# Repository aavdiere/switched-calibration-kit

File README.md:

# Switched Calibration Kit (SCal)
DIY calibration module that automatically switches between calibration standards.
The idea is to use of the shelf RF switches with simple SMD resistors, which can be characterized using a reference measurement of a VNA and then used as a standard.

This is a data based approach is bound to imperfections. The other way would be to make a model of the calibration kit and reference that instead of a measurement.
As it is quite difficult to create a model for the switches without knowing the exact layout, the data approach was preferred.
The SCal is characterised and measured on the same day to avoid temperature fluctuations as they will impact the validity of the reference measurement, temperature control should be added on future revisions.

The boards were manufactured using Aisler's [four layer boards](https://community.aisler.net/t/4-layer-hd-pcb-stackup/86) using the Panasonic Prepreg 1080 Type R-1551(W).
The traces were designed to be 50Ω according to Aisler's recommendations.

## First version - Simple, cheap, proof of concept
Calibration kit using Infineon BGS12PN10/BGS14PN10.
- 2 ports
- 50 Ohm path
- Open path
- Short path
- Through path
- 3dB attenuation path

## Board

*Full populated board. High-end K (2.92mm) connectors were used but are definitely not required. Screw on connectors were used to reduce the solder variability during initial measurements.*

*Close-up picture of the switches and standards. The 50Ω terminations are made using two paralell 100Ω resistors on the bottom left and right. The 3dB attenuator path can be seen in the middle, formed as a Π-network.*

## Measurement method
- Perform ECal using the Keysight N4691D calibration kit and the PNA-X
- Measure all of the standards of the custom ECal and save data with calibration applied (reference) and not applied
- Measure the Rosenberger RPC 2.92mm and save data with calibration applied (reference) and not applied
- Attach additional cable to existing cables
- Measure all of the standards of the custom ECal and save raw data (no calibration, raw)
- Measure the Rosenberger RPC 2.92mm and save raw data (no calibration, raw)
- Using Python and scikit-rf package, create a TwelveTerm network calibration using the measured reference ECal standards as ideals and the measured raw ECal standards as measured
- Use this error network to calibrate out the raw measurements of the Rosenberger calibration kit and compare them with the reference measurements

An additional measurement would be a repeatability test:
- Repeatedly measure short/open/load/through standards, making sure you unscrew and screw a different standard in and out each time
- Create the error network using all possible combinations of these measurements
- Measure the variance in error network parameters
- Do the same with the ECal (screw/unscrew after each run), the variance in parameters should be lower considering you don't need to unscrew/screw after measuring each standard

## Results

*Raw measurements of each of the standards. From the open and the short the port offset is visible as is the frequency dependent loss. The through result shows the bandwidth associated with the switches as well as the traces.*

*Comparing the results from the SCal to the Keysight N4691D ECal, we can see comparible results, which look promising.*

*Differences in the measured load, somehow the SCal provides better results than the N4691D.*

*Here we can see the limitations of the measurements/switches. The measured through is nicely characterised up to around 3GHz, after which the SCal starts to deviate.*

## Remarks
The currently used silkscreen is confusing and prone to interconnection errors.
It might be a good idea to allow for rotational symmetry in the connector or to simply swap the legend around.

When looking at the load on the SCal, the S-parameters show that it starts of quite capacitive, which is odd.
This makes modelling it with typical methods difficult.
Maybe removing the whole top ground plane could fix that and only relying on microstrip lines.

The attenuator (not shown) doesn't have good performance, not even close.
Maybe using smaller resistors or a dedicated attenuator chip would be better.

The open and short standard should be located af far away from each other as possible as not to resonate.

The switches used have a minimum frequency in the datasheet.
This minimum frequency was ignored here and did not show up in the results.
However, if they are using PIN diodes to do the switching, the inductors used might not be good enough at lower frequencies, so watch out.

Overall the SCal has very nice results and could be usable for lower frequency measurements.

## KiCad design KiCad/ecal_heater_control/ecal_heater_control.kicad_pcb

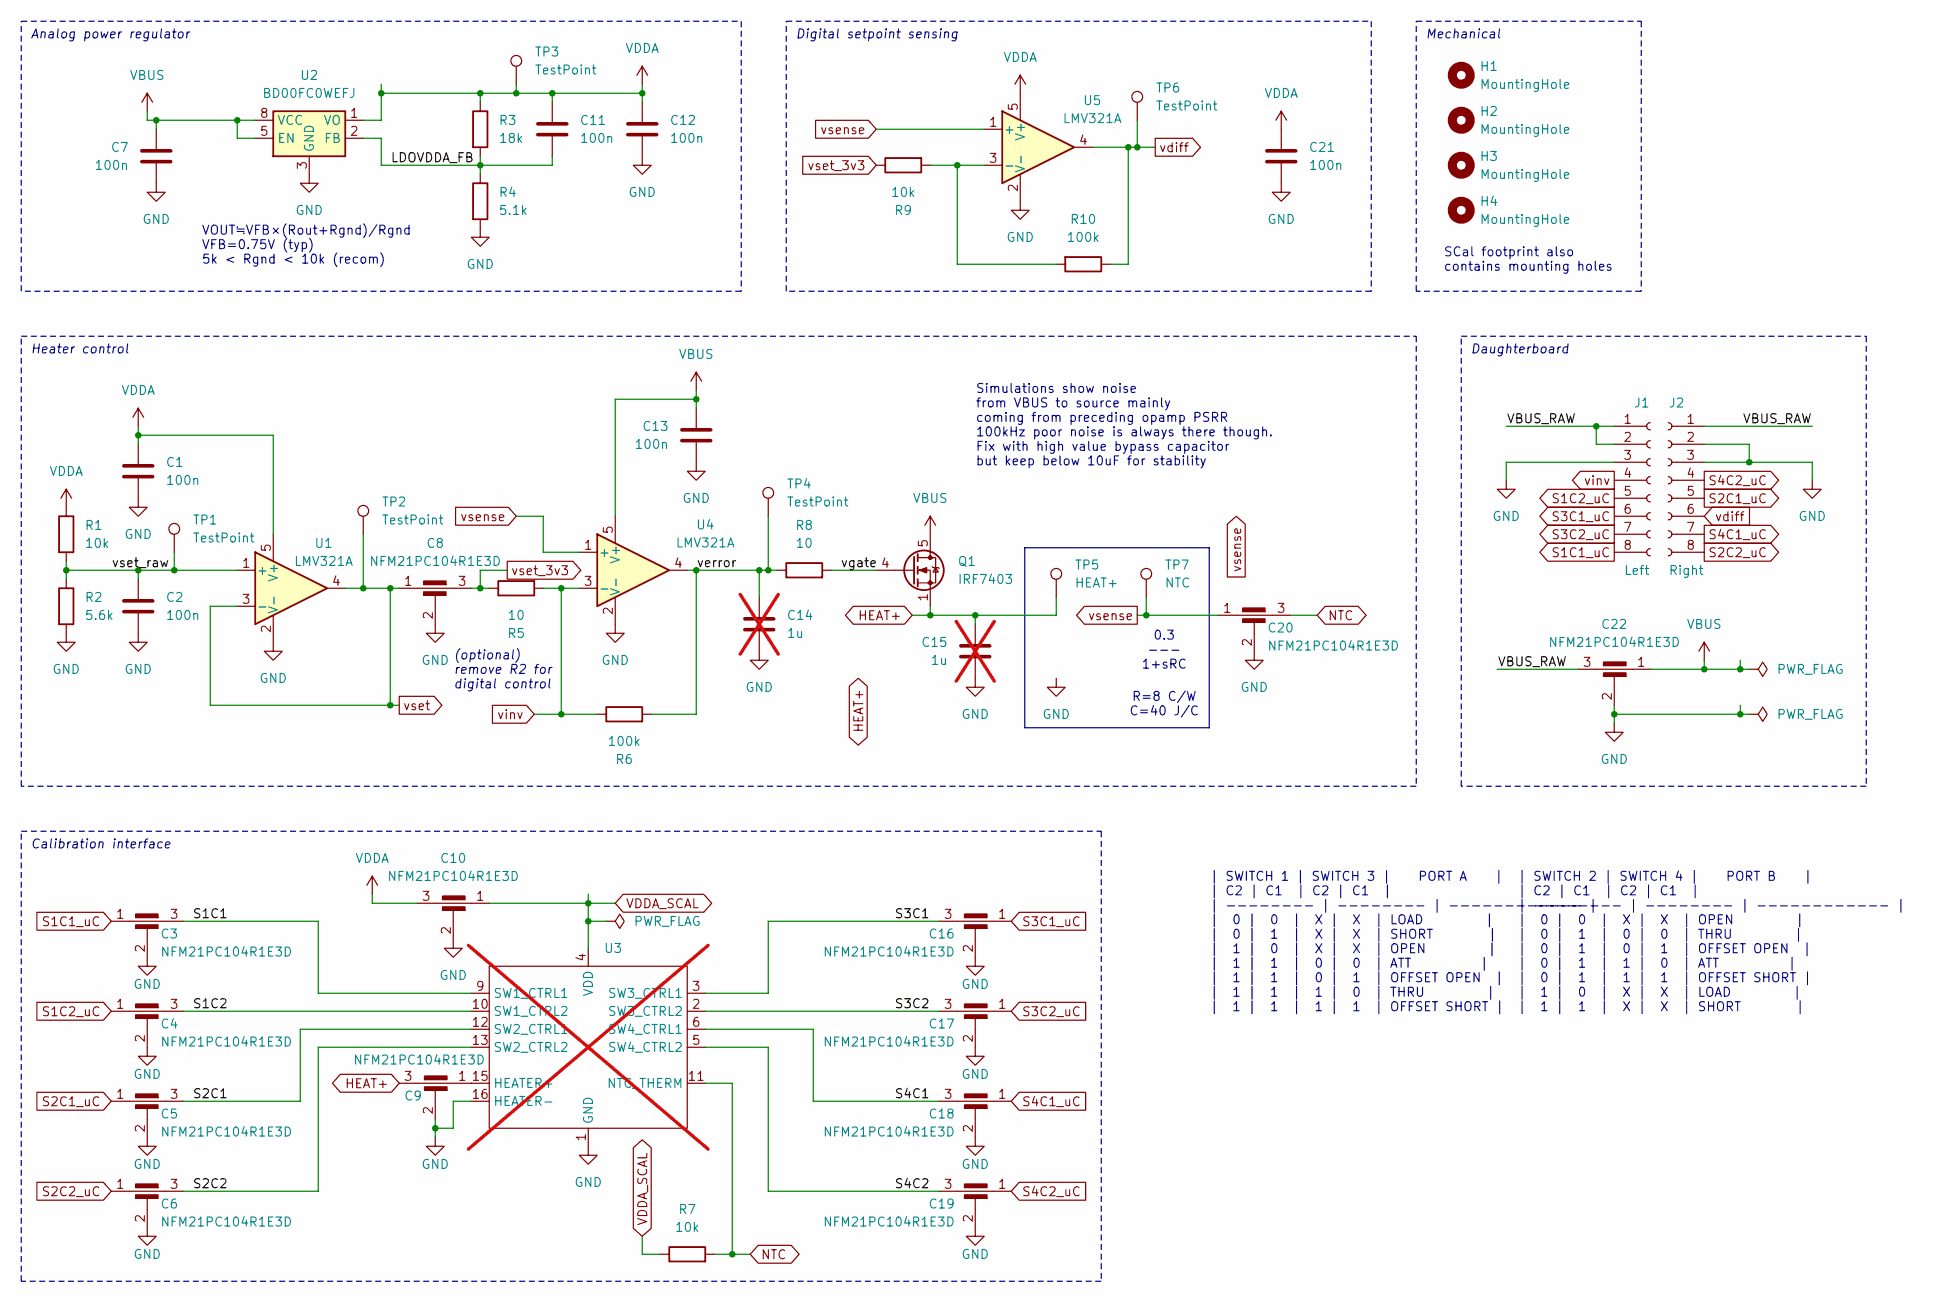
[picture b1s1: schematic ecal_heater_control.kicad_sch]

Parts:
C1, C2, C7, C11, C12, C13, C21: 100n; C_0402_1005Metric
C3, C4, C5, C6, C8, C9, C10, C16, C17, C18, C19, C20, C22: NFM21PC104R1E3D; NFM21PC
C14, C15: 1u; C_0603_1608Metric; not fitted
H1, H2, H3, H4: MountingHole; MountingHole_3.2mm_M3_DIN965
J1: Left; PinSocket_1x08_P2.54mm_Vertical
J2: Right; PinSocket_1x08_P2.54mm_Vertical
Q1: IRF7403; SOIC-8_3.9x4.9mm_P1.27mm
R1, R7, R9: 10k; R_0402_1005Metric
R2: 5.6k; R_0402_1005Metric
R3: 18k; R_0402_1005Metric
R4: 5.1k; R_0402_1005Metric
R5, R8: 10; R_0402_1005Metric
R6, R10: 100k; R_0402_1005Metric
TP1, TP2, TP3, TP4, TP6: TestPoint; TestPoint_Pad_D1.0mm
TP5: HEAT+; TestPoint_Pad_D1.0mm
TP7: NTC; TestPoint_Pad_D1.0mm
U1, U4, U5: LMV321A; SOT-23-5
U2: BD00FC0WEFJ; HTSOP-8-1EP_3.9x4.9mm_P1.27mm_EP2.4x3.2mm
U3: SCAL; not fitted

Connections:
/LDOVDDA_FB: C11.2, R3.2, R4.1, U2.2 (FB)
/S1C1: C3.3, U3.9 (SW1_CTRL1)
/S1C2: C4.3, U3.10 (SW1_CTRL2)
/S2C1: C5.3, U3.12 (SW2_CTRL1)
/S2C2: C6.3, U3.13 (SW2_CTRL2)
/S3C1: C16.3, U3.3 (SW3_CTRL1)
/S3C2: C17.3, U3.2 (SW3_CTRL2)
/S4C1: C18.3, U3.6 (SW4_CTRL1)
/S4C2: C19.3, U3.5 (SW4_CTRL2)
/VBUS_RAW: C22.3, J1.1, J1.2, J2.1
/verror: C14.1, R6.2, R8.1, TP4.1 (1_1), U4.4
/vgate: Q1.4 (G), R8.2
/vset_raw: C2.1, R1.2, R2.1, TP1.1 (1_1), U1.1 (+)
GND: C1.2, C2.2, C3.2, C4.2, C5.2, C6.2, C7.2, C8.2, C9.2, C10.2, C12.2, C13.2, C14.2, C15.2, C16.2, C17.2, C18.2, C19.2, C20.2, C21.2, C22.2, J1.3, J2.2, J2.3, R2.2, R4.2, U1.2 (V-), U2.3 (GND), U2.9 (GND), U3.1 (GND), U3.7 (GND), U3.8 (GND), U3.14 (GND), U3.16 (HEATER-), U4.2 (V-), U5.2 (V-)
HEAT+: C9.3, C15.1, Q1.1 (S), Q1.2 (S), Q1.3 (S), TP5.1 (1_1)
NTC: C20.3, R7.2, U3.11 (NTC_THERM)
unnamed: C9.1, U3.15 (HEATER+)
unnamed: R9.2, R10.2, U5.3 (-)
S1C1_uC: C3.1, J1.8
S1C2_uC: C4.1, J1.5
S2C1_uC: C5.1, J2.5
S2C2_uC: C6.1, J2.8
S3C1_uC: C16.1, J1.6
S3C2_uC: C17.1, J1.7
S4C1_uC: C18.1, J2.7
S4C2_uC: C19.1, J2.4
VBUS: C7.1, C13.1, C22.1, Q1.5 (D), Q1.6 (D), Q1.7 (D), Q1.8 (D), U2.5 (EN), U2.8 (VCC), U4.5 (V+)
VDDA: C1.1, C10.3, C11.1, C12.1, C21.1, R1.1, R3.1, TP3.1 (1_1), U1.5 (V+), U2.1 (VO), U5.5 (V+)
VDDA_SCAL: C10.1, R7.1, U3.4 (VDD)
vdiff: J2.6, R10.1, TP6.1 (1_1), U5.4
vinv: J1.4, R5.2, R6.1, U4.3 (-)
vsense: C20.1, TP7.1 (1_1), U4.1 (+), U5.1 (+)
vset: C8.1, TP2.1 (1_1), U1.3 (-), U1.4
vset_3v3: C8.3, R5.1, R9.1

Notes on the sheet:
Daughterboard
Digital setpoint sensing
VOUT≒VFB×(Rout+Rgnd)/Rgnd VFB=0.75V (typ) 5k < Rgnd < 10k (recom)
Heater control
0.3 --- 1+sRC
Analog power regulator
SCal footprint also contains mounting holes
Calibration interface
Simulations show noise from VBUS to source mainly coming from preceding opamp PSRR 100kHz poor noise is always there though. Fix with high value bypass capacitor but keep below 10uF for stability
(optional) remove R2 for digital control
R=8 C/W C=40 J/C
Mechanical
| SWITCH 1 | SWITCH 3 | PORT A | | C2 | C1 | C2 | C1 | | -------- | -------- | ------------ | | 0 | 0 | X | X | LOAD | | 0 | 1 | X | X | SHORT | | 1 | 0 | X | X | OPEN | | 1 | 1 | 0 | 0 | ATT | | 1 | 1 | 0 | 1 | OFFSET OPEN | | 1 | 1 | 1 | 0 | THRU | | 1 | 1 | 1 | 1 | OFFSET SHORT |
| SWITCH 2 | SWITCH 4 | PORT B | | C2 | C1 | C2 | C1 | | -------- | -------- | ------------ | | 0 | 0 | X | X | OPEN | | 0 | 1 | 0 | 0 | THRU | | 0 | 1 | 0 | 1 | OFFSET OPEN | | 0 | 1 | 1 | 0 | ATT | | 0 | 1 | 1 | 1 | OFFSET SHORT | | 1 | 0 | X | X | LOAD | | 1 | 1 | X | X | SHORT |

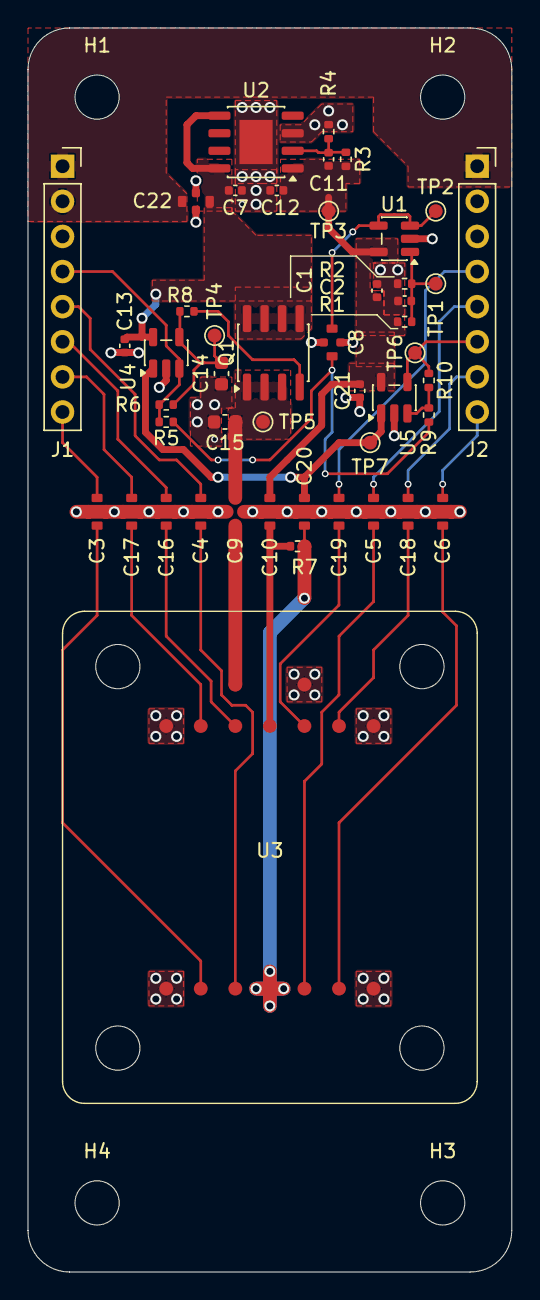
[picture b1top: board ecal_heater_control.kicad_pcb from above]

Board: 2 copper layers, 35.0 x 90.0 mm, 51 parts (0 on the bottom side), 34 nets.

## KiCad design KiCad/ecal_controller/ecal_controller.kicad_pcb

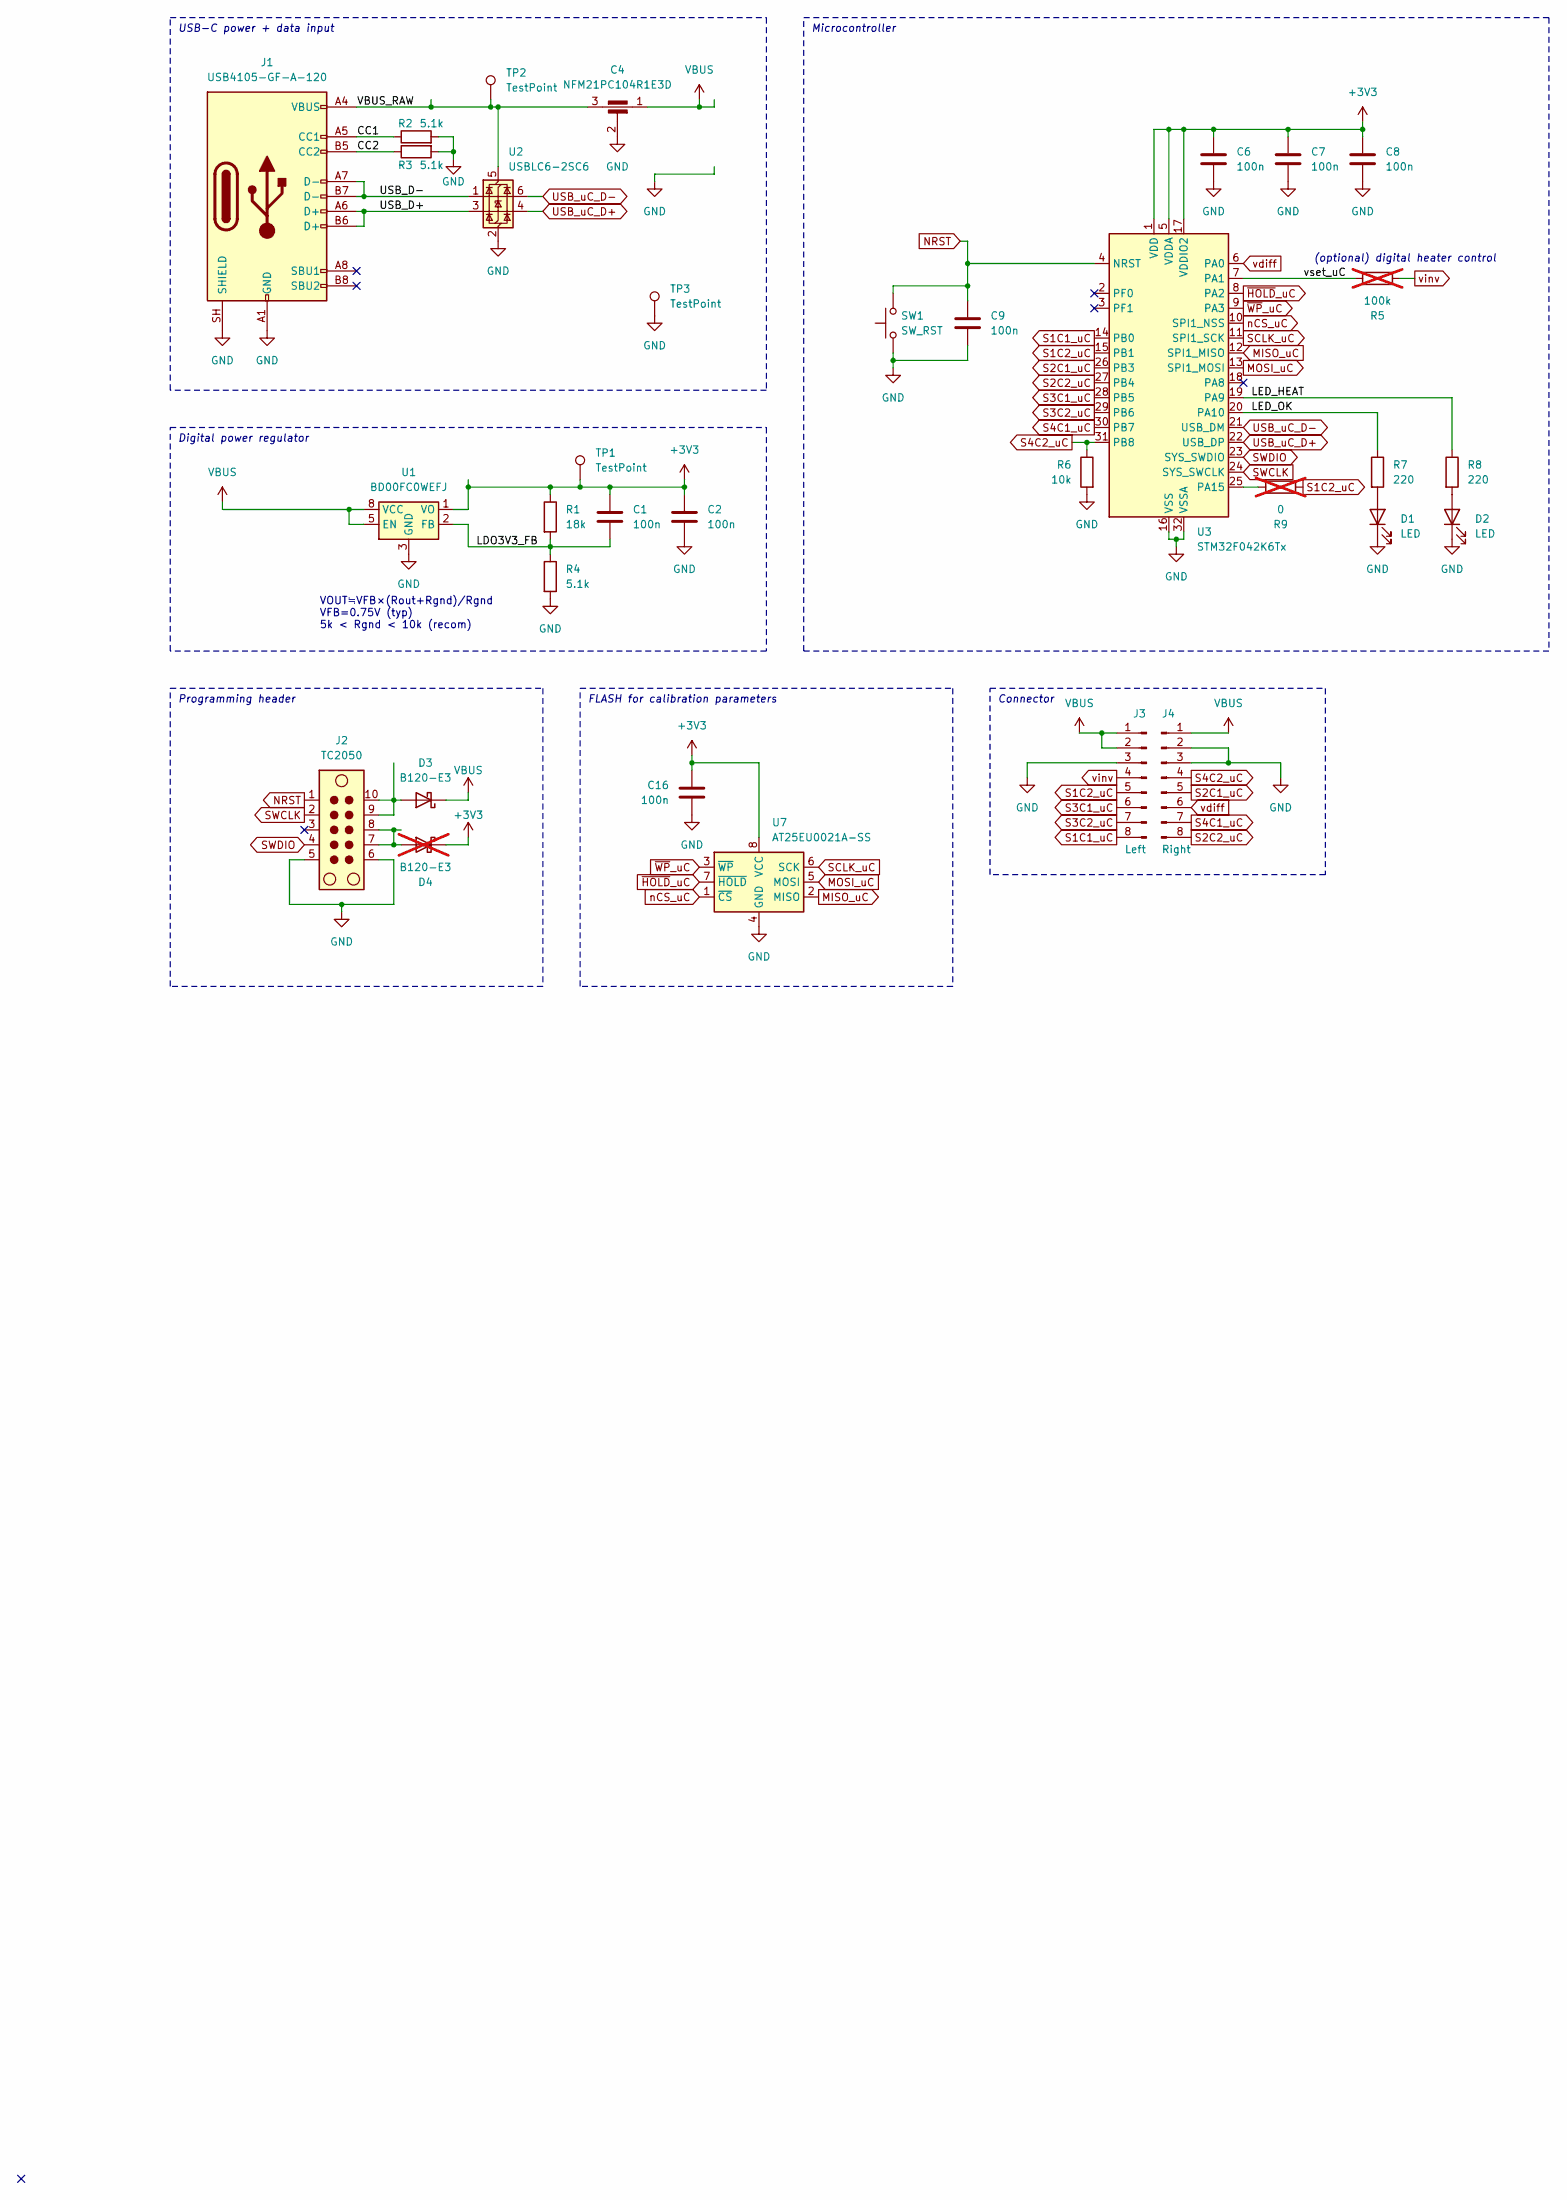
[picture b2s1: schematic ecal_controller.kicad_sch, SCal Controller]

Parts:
C1, C2, C6, C7, C8, C9, C16: 100n; C_0402_1005Metric
C4: NFM21PC104R1E3D; NFM21PC
D1, D2: LED; LED_0603_1608Metric
D3: B120-E3; D_SMA
D4: B120-E3; D_SMA; not fitted
J1: USB4105-GF-A-120; USB_C_Receptacle_GCT_USB4110
J2: TC2050; Tag-Connect_TC2050-IDC-FP_2x05_P1.27mm_Vertical
J3: Left; PinHeader_1x08_P2.54mm_Vertical
J4: Right; PinHeader_1x08_P2.54mm_Vertical
R1: 18k; R_0402_1005Metric
R2, R3, R4: 5.1k; R_0402_1005Metric
R5: 100k; R_0402_1005Metric; not fitted
R6: 10k; R_0402_1005Metric
R7, R8: 220; R_0402_1005Metric
R9: 0; R_0402_1005Metric; not fitted
SW1: SW_RST; SW_Push_1P1T_NO_E-Switch_TL3301NxxxxxG
TP1, TP2, TP3: TestPoint; TestPoint_Pad_D1.0mm
U1: BD00FC0WEFJ; HTSOP-8-1EP_3.9x4.9mm_P1.27mm_EP2.4x3.2mm
U2: USBLC6-2SC6; SOT-23-6
U3: STM32F042K6Tx; LQFP-32_7x7mm_P0.8mm
U7: AT25EU0021A-SS; SOIC-8_3.9x4.9mm_P1.27mm

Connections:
+3V3: C1.1, C2.1, C6.1, C7.1, C8.1, C16.1, D4.1 (K), R1.1, TP1.1 (1_1), U1.1 (VO), U3.1 (VDD), U3.5 (VDDA), U3.17 (VDDIO2), U7.8 (VCC)
/CC1: J1.A5 (CC1), R2.1
/CC2: J1.B5 (CC2), R3.1
/LDO3V3_FB: C1.2, R1.2, R4.1, U1.2 (FB)
/LED_HEAT: R8.1, U3.19 (PA9)
/LED_OK: R7.1, U3.20 (PA10)
/USB_D+: J1.A6 (D+), J1.B6 (D+), U2.3 (I/O2)
/USB_D-: J1.A7 (D-), J1.B7 (D-), U2.1 (I/O1)
/VBUS_RAW: C4.3, J1.A4 (VBUS), J1.A9 (VBUS), J1.B4 (VBUS), J1.B9 (VBUS), TP2.1 (1_1), U2.5 (VBUS)
/vset_uC: R5.1, U3.7 (PA1)
GND: C2.2, C4.2, C6.2, C7.2, C8.2, C9.2, C16.2, D1.1 (K), D2.1 (K), J1.A1 (GND), J1.A12 (GND), J1.B1 (GND), J1.B12 (GND), J1.SH (SHIELD), J2.5, J2.6, J3.3, J4.2, J4.3, R2.2, R3.2, R4.2, R6.2, SW1.1, TP3.1 (1_1), U1.3 (GND), U1.9 (GND), U2.2 (GND), U3.16 (VSS), U3.32 (VSSA), U7.4 (GND)
MISO_uC: U3.12 (SPI1_MISO), U7.2 (MISO)
MOSI_uC: U3.13 (SPI1_MOSI), U7.5 (MOSI)
NRST: C9.1, J2.1, SW1.2, U3.4 (NRST)
unnamed: D1.2 (A), R7.2
unnamed: D2.2 (A), R8.2
unnamed: D3.2 (A), J2.9, J2.10
unnamed: D4.2 (A), J2.7, J2.8
unnamed: R9.1, U3.25 (PA15)
S1C1_uC: J3.8, U3.14 (PB0)
S1C2_uC: J3.5, R9.2, U3.15 (PB1)
S2C1_uC: J4.5, U3.26 (PB3)
S2C2_uC: J4.8, U3.27 (PB4)
S3C1_uC: J3.6, U3.28 (PB5)
S3C2_uC: J3.7, U3.29 (PB6)
S4C1_uC: J4.7, U3.30 (PB7)
S4C2_uC: J4.4, R6.1, U3.31 (PB8)
SCLK_uC: U3.11 (SPI1_SCK), U7.6 (SCK)
SWCLK: J2.2, U3.24 (SYS_SWCLK)
SWDIO: J2.4, U3.23 (SYS_SWDIO)
USB_uC_D+: U2.4 (I/O2), U3.22 (USB_DP)
USB_uC_D-: U2.6 (I/O1), U3.21 (USB_DM)
VBUS: C4.1, D3.1 (K), J3.1, J3.2, J4.1, U1.5 (EN), U1.8 (VCC)
nCS_uC: U3.10 (SPI1_NSS), U7.1 (~CS)
vdiff: J4.6, U3.6 (PA0)
vinv: J3.4, R5.2
~HOLD_uC: U3.8 (PA2), U7.7 (~HOLD)
~WP_uC: U3.9 (PA3), U7.3 (~WP)

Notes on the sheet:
Digital power regulator
VOUT≒VFB×(Rout+Rgnd)/Rgnd VFB=0.75V (typ) 5k < Rgnd < 10k (recom)
USB-C power + data input
Programming header
FLASH for calibration parameters
Connector
(optional) digital heater control
Microcontroller

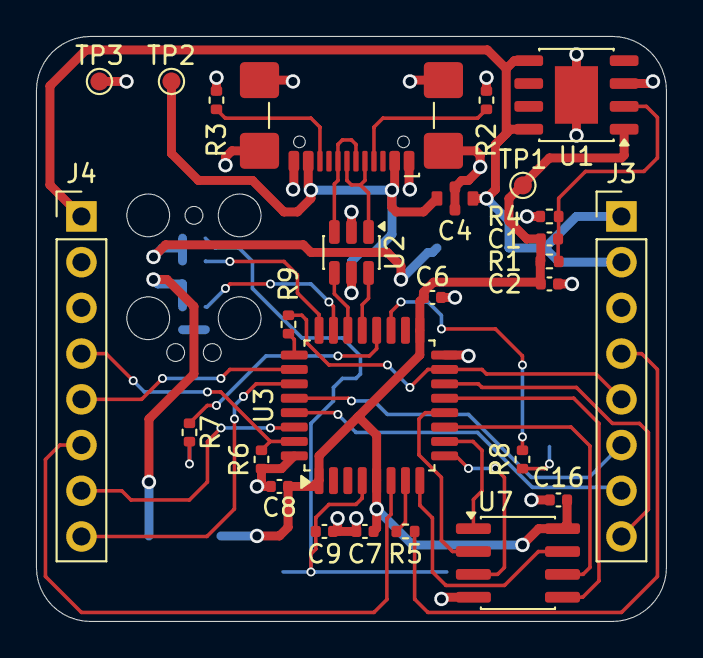
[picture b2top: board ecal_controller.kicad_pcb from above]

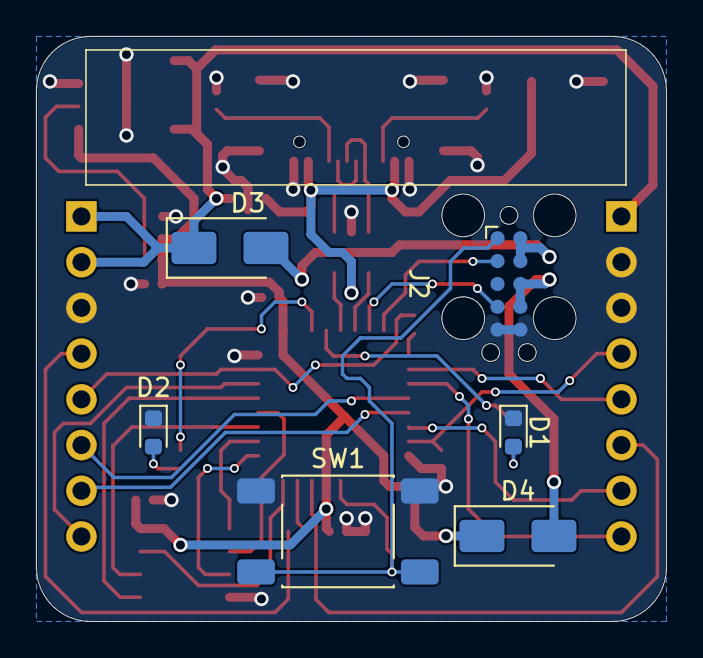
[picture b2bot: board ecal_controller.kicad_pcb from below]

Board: 2 copper layers, 35.0 x 32.5 mm, 33 parts (6 on the bottom side), 38 nets.

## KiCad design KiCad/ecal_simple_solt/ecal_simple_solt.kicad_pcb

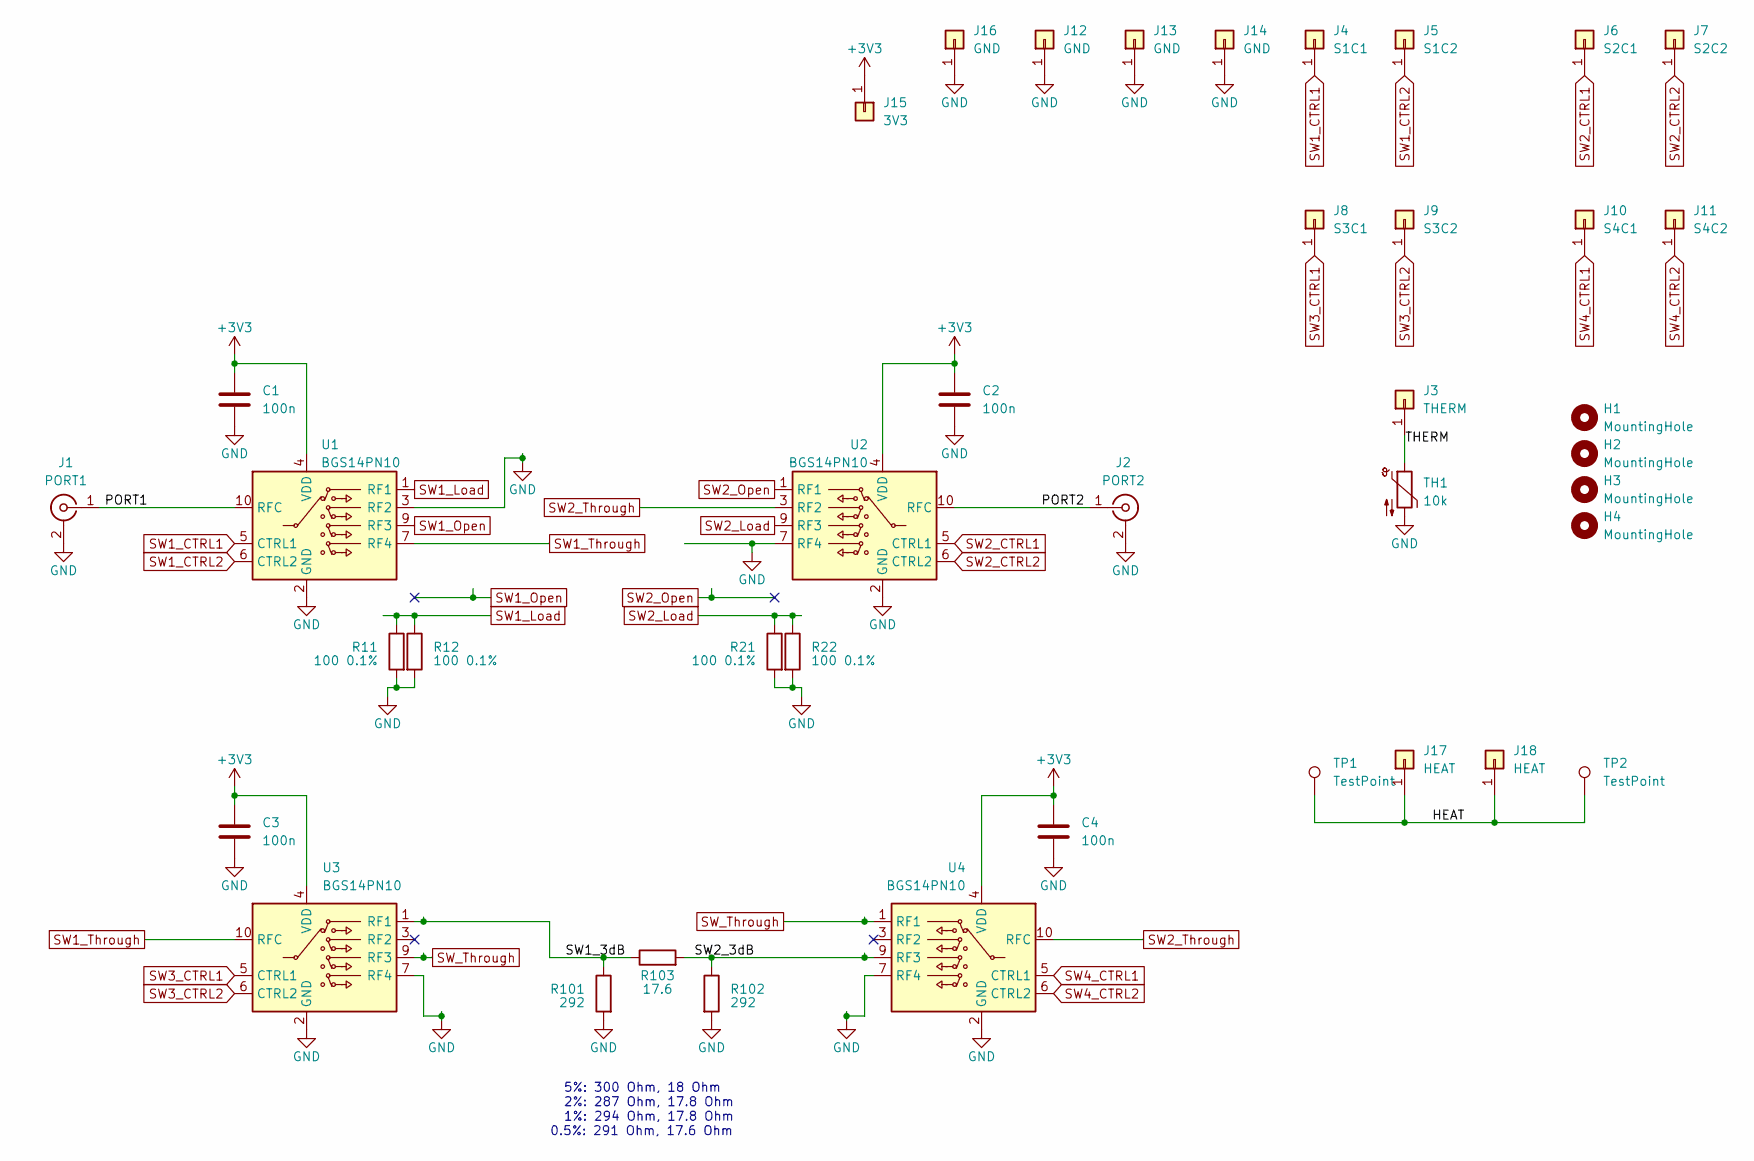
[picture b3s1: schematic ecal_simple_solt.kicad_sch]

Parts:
C1, C2, C3, C4: 100n; C_0402_1005Metric
H1, H2, H3, H4: MountingHole; MountingHole_3.2mm_M3_ISO7380
J1: PORT1; 32K243-40ML5; MPN 32K243-40ML5; Mouser No 476-32K243-40ML5
J2: PORT2; 32K243-40ML5; MPN 32K243-40ML5; Mouser No 476-32K243-40ML5
J3: THERM; CPG-01-TH-B; MPN CPG-01-TH-B
J4: S1C1; CPG-01-TH-B; MPN CPG-01-TH-B
J5: S1C2; CPG-01-TH-B; MPN CPG-01-TH-B
J6: S2C1; CPG-01-TH-B; MPN CPG-01-TH-B
J7: S2C2; CPG-01-TH-B; MPN CPG-01-TH-B
J8: S3C1; CPG-01-TH-B; MPN CPG-01-TH-B
J9: S3C2; CPG-01-TH-B; MPN CPG-01-TH-B
J10: S4C1; CPG-01-TH-B; MPN CPG-01-TH-B
J11: S4C2; CPG-01-TH-B; MPN CPG-01-TH-B
J12, J13, J14, J16: GND; CPG-01-TH-B; MPN CPG-01-TH-B
J15: 3V3; CPG-01-TH-B; MPN CPG-01-TH-B
J17, J18: HEAT; CPG-01-TH-B; MPN CPG-01-TH-B
R11, R12, R21, R22: 100 0.1%; R_0201_0603Metric
R101, R102: 292; R_0402_1005Metric
R103: 17.6; R_0402_1005Metric
TH1: 10k; R_0402_1005Metric; MPN NCU15XH103D60RC; Mouser No 81-NCU15XH103D60RC
TP1, TP2: TestPoint; TestPoint_Pad_1.0x1.0mm
U1, U2, U3, U4: BGS14PN10; XQFP-10; MPN BGS14PN10E6327XTSA1; Mouser No 726-BGS14PN10E6327X

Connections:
+3V3: C1.1, C2.1, C3.1, C4.1, J15.1 (Pin_1_1), U1.4 (VDD), U2.4 (VDD), U3.4 (VDD), U4.4 (VDD)
/HEAT: J17.1 (Pin_1_1), J18.1 (Pin_1_1), TP1.1 (1_1), TP2.1 (1_1)
/PORT1: J1.1 (In), U1.10 (RFC)
/PORT2: J2.1 (In), U2.10 (RFC)
/SW1_3dB: R101.1, R103.1, U3.1 (RF1)
/SW2_3dB: R102.1, R103.2, U4.9 (RF3)
/THERM: J3.1 (Pin_1_1), TH1.1
GND: C1.2, C2.2, C3.2, C4.2, J1.2 (Ext), J2.2 (Ext), J12.1 (Pin_1_1), J13.1 (Pin_1_1), J14.1 (Pin_1_1), J16.1 (Pin_1_1), R11.2, R12.2, R21.2, R22.2, R101.2, R102.2, TH1.2, U1.2 (GND), U1.3 (RF2), U1.8 (GND), U2.2 (GND), U2.7 (RF4), U2.8 (GND), U3.2 (GND), U3.7 (RF4), U3.8 (GND), U4.2 (GND), U4.7 (RF4), U4.8 (GND)
SW1_CTRL1: J4.1 (Pin_1_1), U1.5 (CTRL1)
SW1_CTRL2: J5.1 (Pin_1_1), U1.6 (CTRL2)
SW1_Load: R11.1, R12.1, U1.1 (RF1)
SW1_Open: U1.9 (RF3)
SW1_Through: U1.7 (RF4), U3.10 (RFC)
SW2_CTRL1: J6.1 (Pin_1_1), U2.5 (CTRL1)
SW2_CTRL2: J7.1 (Pin_1_1), U2.6 (CTRL2)
SW2_Load: R21.1, R22.1, U2.9 (RF3)
SW2_Open: U2.1 (RF1)
SW2_Through: U2.3 (RF2), U4.10 (RFC)
SW3_CTRL1: J8.1 (Pin_1_1), U3.5 (CTRL1)
SW3_CTRL2: J9.1 (Pin_1_1), U3.6 (CTRL2)
SW4_CTRL1: J10.1 (Pin_1_1), U4.5 (CTRL1)
SW4_CTRL2: J11.1 (Pin_1_1), U4.6 (CTRL2)
SW_Through: U3.9 (RF3), U4.1 (RF1)

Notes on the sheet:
5%: 300 Ohm, 18 Ohm 2%: 287 Ohm, 17.8 Ohm 1%: 294 Ohm, 17.8 Ohm 0.5%: 291 Ohm, 17.6 Ohm

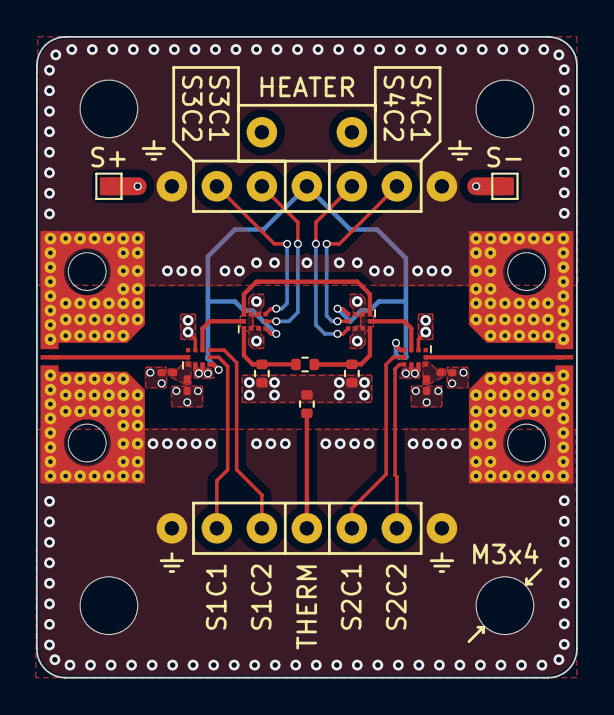
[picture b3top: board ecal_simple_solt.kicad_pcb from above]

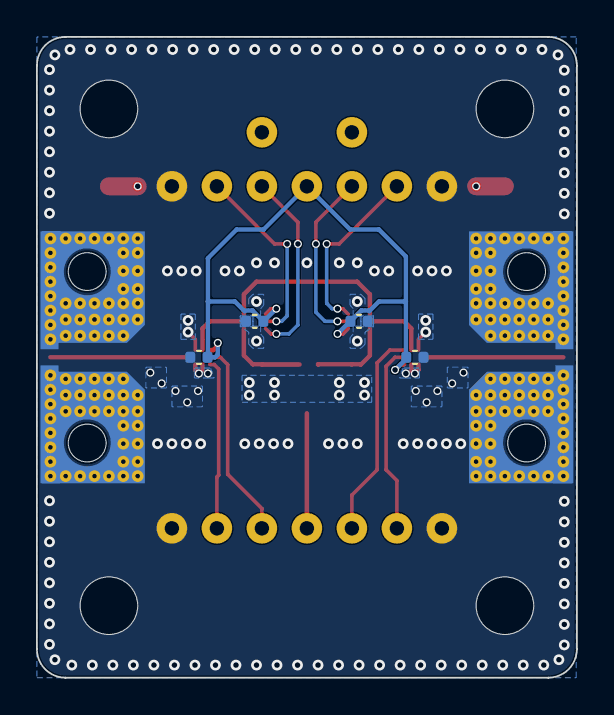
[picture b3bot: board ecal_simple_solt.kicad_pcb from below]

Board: 4 copper layers, 30.0 x 35.6 mm, 40 parts (20 on the bottom side), 21 nets.

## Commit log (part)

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2023-07-07 Add PCB
2023-07-07 Add text
